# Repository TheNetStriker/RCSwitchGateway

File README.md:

# RCSwitchGateway
## Description
This program uses a modified version of the [rc-switch library](https://github.com/sui77/rc-switch) to control 433 MHZ based switches using MQTT commands over Wifi. It runs on [ESP32](https://www.espressif.com/en/products/hardware/esp32/overview) microcontrollers. (Currently only tested with Adafruit Huzzah32) This program can also detect 433 MHZ signals and send them back via MQTT. Currently it only supports sending **Type A** signals and can also receive commands from e.g. König SAS-SA200 and SAS-SA2002 smoke detectors. Please look at the [RC Switch Wiki](https://github.com/sui77/rc-switch/wiki/Add_New_Remote_Part_1) on how to implement more signals.
## Installation
- Install the ESP32 on the Arduino IDE as described [here](https://randomnerdtutorials.com/installing-the-esp32-board-in-arduino-ide-windows-instructions/).
- Clone the project and create an **Defines.h** file containing the following information:
```cpp
#define WLAN_SSID "MYSSID"
#define WLAN_PASSWORD "MYPASSWORD"
#define MQTT_BROKER_IP "MYIP"
#define HOSTNAME "MYHOSTNAME"
```
## OTA Update
To enable OTA update just set **default_envs** to **release** and add an ota.txt file containing the ip of the device and a password on separate lines. The **ota.py** file will automatically add the required configuration for the OTA upload.
## Hardware
In the **Eagle** folder you can find Eagle and Gerber files for a feather board to connect a MX-05V receiver and an FS1000A sender to the Adafruit Huzzah32.
## MQTT commands and events
The MQTT messages follow the [Homie standard](https://homieiot.github.io/) and the device will be automatically autodetected on controllers that support this standard.
### Sender
Commands are sent as json text.\
**homie/hostname/sender/sendtypea**: Command to send a type A RC Signal with the following settings:
`{"group": "11111", "device": "11111", "repeatTransmit": 5, "switchOnOff": true}`\
**homie/hostname/sender/send**: Command to send a custom signal with the following attributes:
`{"code": 1234, "codeLength": 24, "protocol": 1, "repeatTransmit": 5 }`
### Receiver
The receiver is just sending plain numbers.\
**homie/hostname/receiver/queuelength**: Length of the current queue of signals to be sent.\
**homie/rcswitch01/receiver/codereceived**: Received code event
### System
The device also sends some system values.\
**homie/rcswitch01/system/rssi**: The device send's the wifi signal strength every minute to this topic.\
**homie/rcswitch01/system/log**: At the moment this just send's an "Startup" message when the device started. This helps to find out if the device crashed at some point.

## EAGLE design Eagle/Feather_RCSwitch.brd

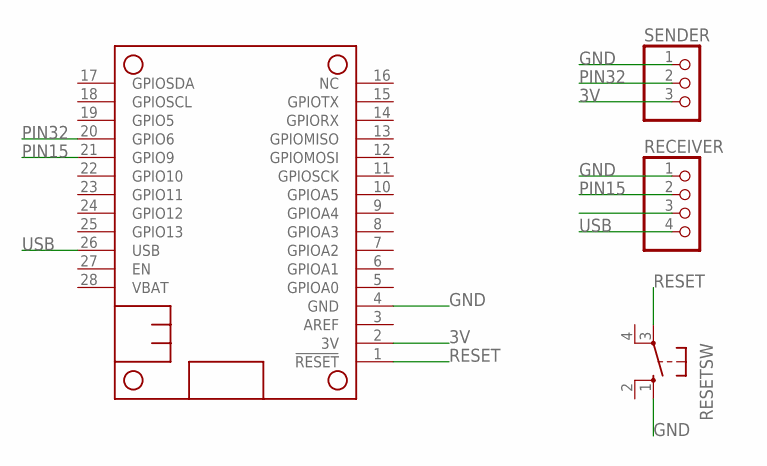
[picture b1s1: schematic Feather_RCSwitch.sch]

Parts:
MS1: FEATHERWING
RECEIVER: PINHD-1X4; 1X04
RESETSW: 10-XX; B3F-10XX
SENDER: PINHD-1X3; 1X03

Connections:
3V: MS1.2 (3V), SENDER.3
GND: MS1.4 (GND), RECEIVER.1, RESETSW.1 (S), SENDER.1
PIN15: MS1.21 (GPIO9), RECEIVER.2
PIN32: MS1.20 (GPIO6), SENDER.2
RESET: MS1.1 (!RESET), RESETSW.3
USB: MS1.26 (USB), RECEIVER.4

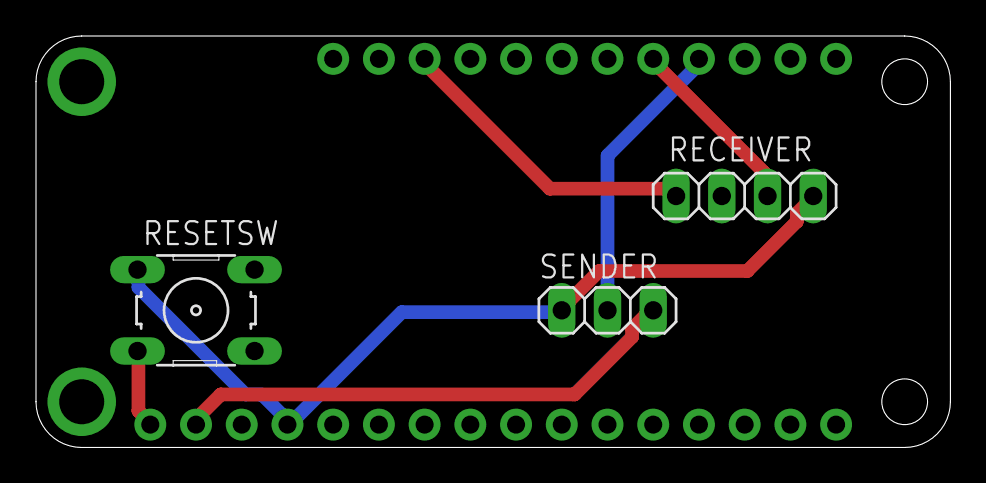
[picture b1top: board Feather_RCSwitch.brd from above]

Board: 2 copper layers, 50.8 x 22.9 mm, 4 parts (0 on the bottom side), 6 nets.

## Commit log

2019-03-04 Initial commit
    Initial commit
2019-03-05 Readme updated.
2019-04-15 Changed to PlatformIO
    Changed project to PlatformIO
2019-04-15 PlatformIO file updates.
    PlatformIO file updates.
2019-11-22 PlatformIO Version and connect message added.
2020-06-09 WifiManager added to configure the device.
2020-06-10 Switch to PubSubClient. Wifi reconnect implemented.
2020-06-10 Removed doubled functions.
2020-06-10 Restart ESP if auto connect failed.
2020-06-15 Added OTA update.
2020-06-15 Added default password if ota.txt does not exist.
2020-09-11 MQTT LWT message added.
2020-09-11 LWT retain enabled.
2020-09-11 MQTT KeepAlive set to 60 seconds.
2020-09-24 Rssi and log MQTT topic added.
2020-10-06 OTA update improved. WiFi hostname set. Serial debug messages optimized.
2020-10-06 RC_SWITCH_DEBUG variable now excludes all Serial messages if set to false.
2020-10-06 Typo fixed.
2020-10-09 Changed MQTT messages to Homie standard.
2020-10-11 Log Topic changed to not retained.
2020-10-13 Removed invalid characters from topics.
2020-11-05 Ready is now also sent on reconnect.
2020-11-05 Code warning fixed.
2020-11-18 Implemented fast wifi connect to connect to best wifi.
2020-11-24 Fast connect added.
2020-11-24 Reset MQTT topic added.
2020-11-25 WiFi BSSID is now saved for later reconnect.
2020-11-25 Double Reset Detector is now stopped on OTA update.
2022-11-04 Config portal Timeout added.
